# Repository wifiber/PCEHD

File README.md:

PC Engine / Turbo Grafx HDMI output board (PCEHD)
==============

Overview
--------------------------
PCEHD is a project to deliver HDMI video/audio from the PC Engine/Turbo-Grafx utilizing the digital video bus exposed on the expansion connector. The goal is to take the digital video directly from the console and upscale it to 1080p.

Features
--------------------------
* None yet

TODO
--------------------------
* Finish initial verion of schematic (DONE)
* Finish initial verion of HDL code (need help here)
* Get test PCBs made (PENDING)
* Get HDMI video output working (PENDING)
* Get analog audio encoded into HDMI stream (PENDING)

Long Term TODO
--------------------------
* Optical Drive Emulation (PENDING)
* Flash cart / SD card option (PENDING)

Installation
--------------------------
Attach PCEHD to the expansion port on your PC Engine or Turbo-Grafx console. Enjoy lag free 1080p.

Usage
--------------------------

More info and discussion
--------------------------
See the docs folder for a collection of PC Engine dev material.
There are good schematics online and the TurboGrafx-16 Unit Service Manual provides an excellent block diagram that really makes understanding the interaction of the 3 main HuC62xx chips much easier.

The aim of the PCEHD project is to reproduce the IC112 (HuC6260) inside the FPGA on the PCEHD. HuC6260, the Video Color Encoder, has an internal palette used for the background and sprites. It is made up of 512 9-bit entries. The first 256 entries are for the backgrounds and the last 256 are for the sprites. 
When the console first boots up, the VCE is initialized with palette data from the Hu Card by the CPU. According to the schematics, the data lines from the HU card all have pull-ups to 5v. This is why when you start the console with no game inserted you get a white screen - the VCE palette get filled with all 0xFF for the RGB data, which then returns white on the screen.

Requirement 1. - The FPGA needs to snoop on the CPU -> VCE communication when the console first boots. The FPGA needs to see what the CPU is loading into the VCE internal palette (All 512 entries). This is possible since both the data and address bus are exposed on the expansion connector. So the FPGA should have insight to the CPU -> VCE communication.
Using the FPGA core for the HuC6260, if we are connected to the same address and data bus as the physical VCE, we should be able to get the CPU to update both the physical VCE and the FPGA-VCE at the same time, since the FPGA-VCE is listening at the same address as the VCE inside the console.  

Once the console boots up and the CPU has successfully loaded the VCE pallette, the VDC now comes into play. The VDC and VCE share a 9-bit video bus (This is separate from the data bus the CPU used to load the palette in the steps above). 
The VDC will be placing data on the video bus, this data is a 9-bit address into the VCE palette (9-bits = 512 entries). The VCE takes these addresses, does the lookup into its palette and returns the 9-bit RGB code.  

Requirement 2. - The FPGA needs to snoop on the VDC -> VCE communication. The VDC will be placing addresses on the video bus. Those addresses reference colors stored in the 512 entry VCE palette table. Once the VCE looks up the address, the data it returns is 9-bit RGB data. This 9-bit RGB data is used inside the HuC6260 to generate the analog RGB and composite signals. Assuming the FPGA knows what RGB values are stored in each VCE table entry.(Req 1)
Also, assuming the FPGA knows what the VCE will display next based on what palette address the VDC was placing on the video bus - we should be able to recreate the scanline that the VCE would have displayed. From there its a matter of line-doubling and tweaking to fit the 1080p standard.
Again, using the FPGA core for the HuC6260 should give us a VCE that acts just like the phyiscal one inside the console. Once we have the VCE outputting the RGB data, its a matter of formatting it into the correct HDMI standard.

Thanks to marqs for the OSSC/CPS2_HDMI projects that are the majority of the base material for this project
https://github.com/marqs85

Thanks to the FPGAPCE project on github for a nice HDL example of the entire console.
https://github.com/Torlus/FPGAPCE

Thanks to skum for the very clean and well layed out KiCad symbol and footprint of the expansion connector. Its 69 pins but somehow his symbol is manageable.
https://github.com/skumlos/pcengine-rgb-addon

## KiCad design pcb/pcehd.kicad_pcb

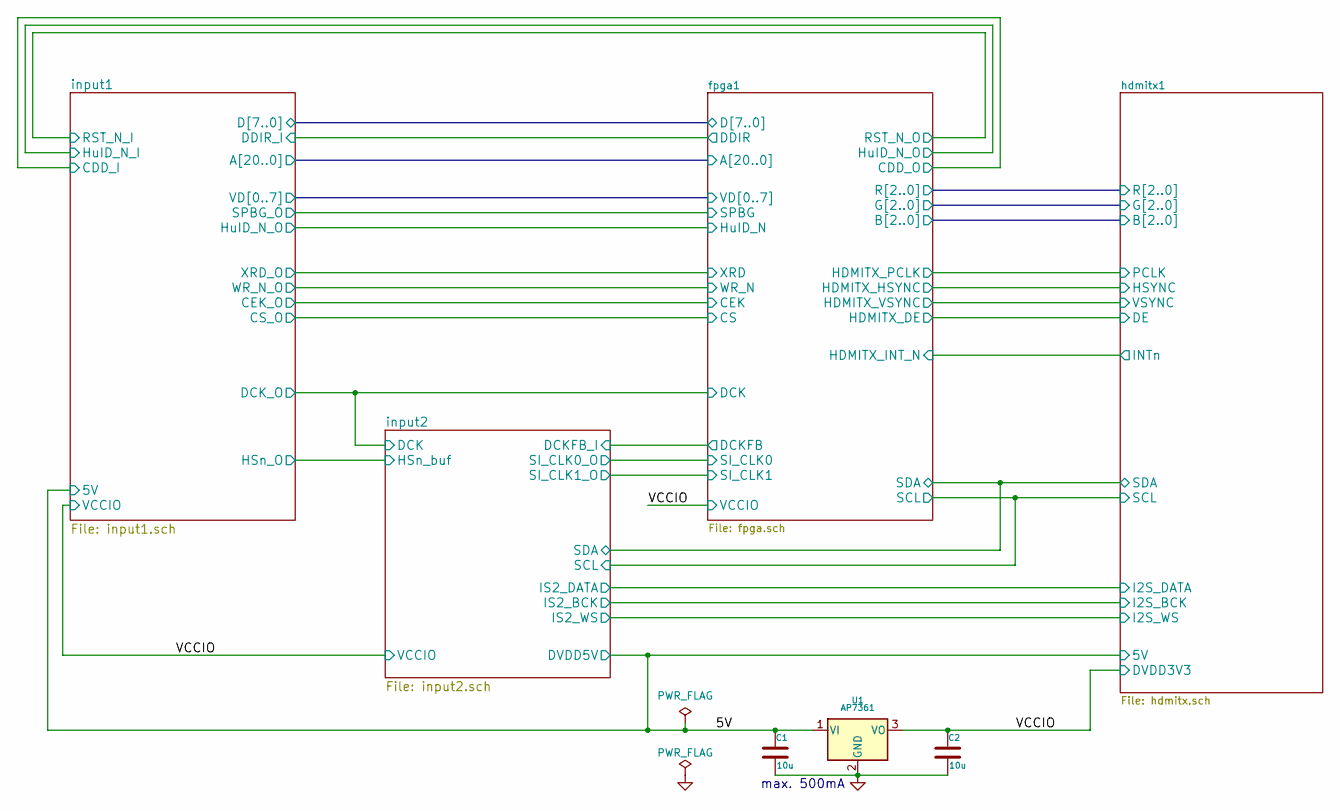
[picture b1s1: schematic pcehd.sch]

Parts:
C1, C2: 10u; SM0603_Capa_libcms
U1: AP7361; SOT-223_Handsoldering

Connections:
/5V: C1.1, U1.1 (VI); also elsewhere on the board
GND: C1.2, C2.2, U1.2 (GND); also elsewhere on the board
VCC: C2.1, U1.3 (VO); also elsewhere on the board

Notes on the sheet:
max. 500mA

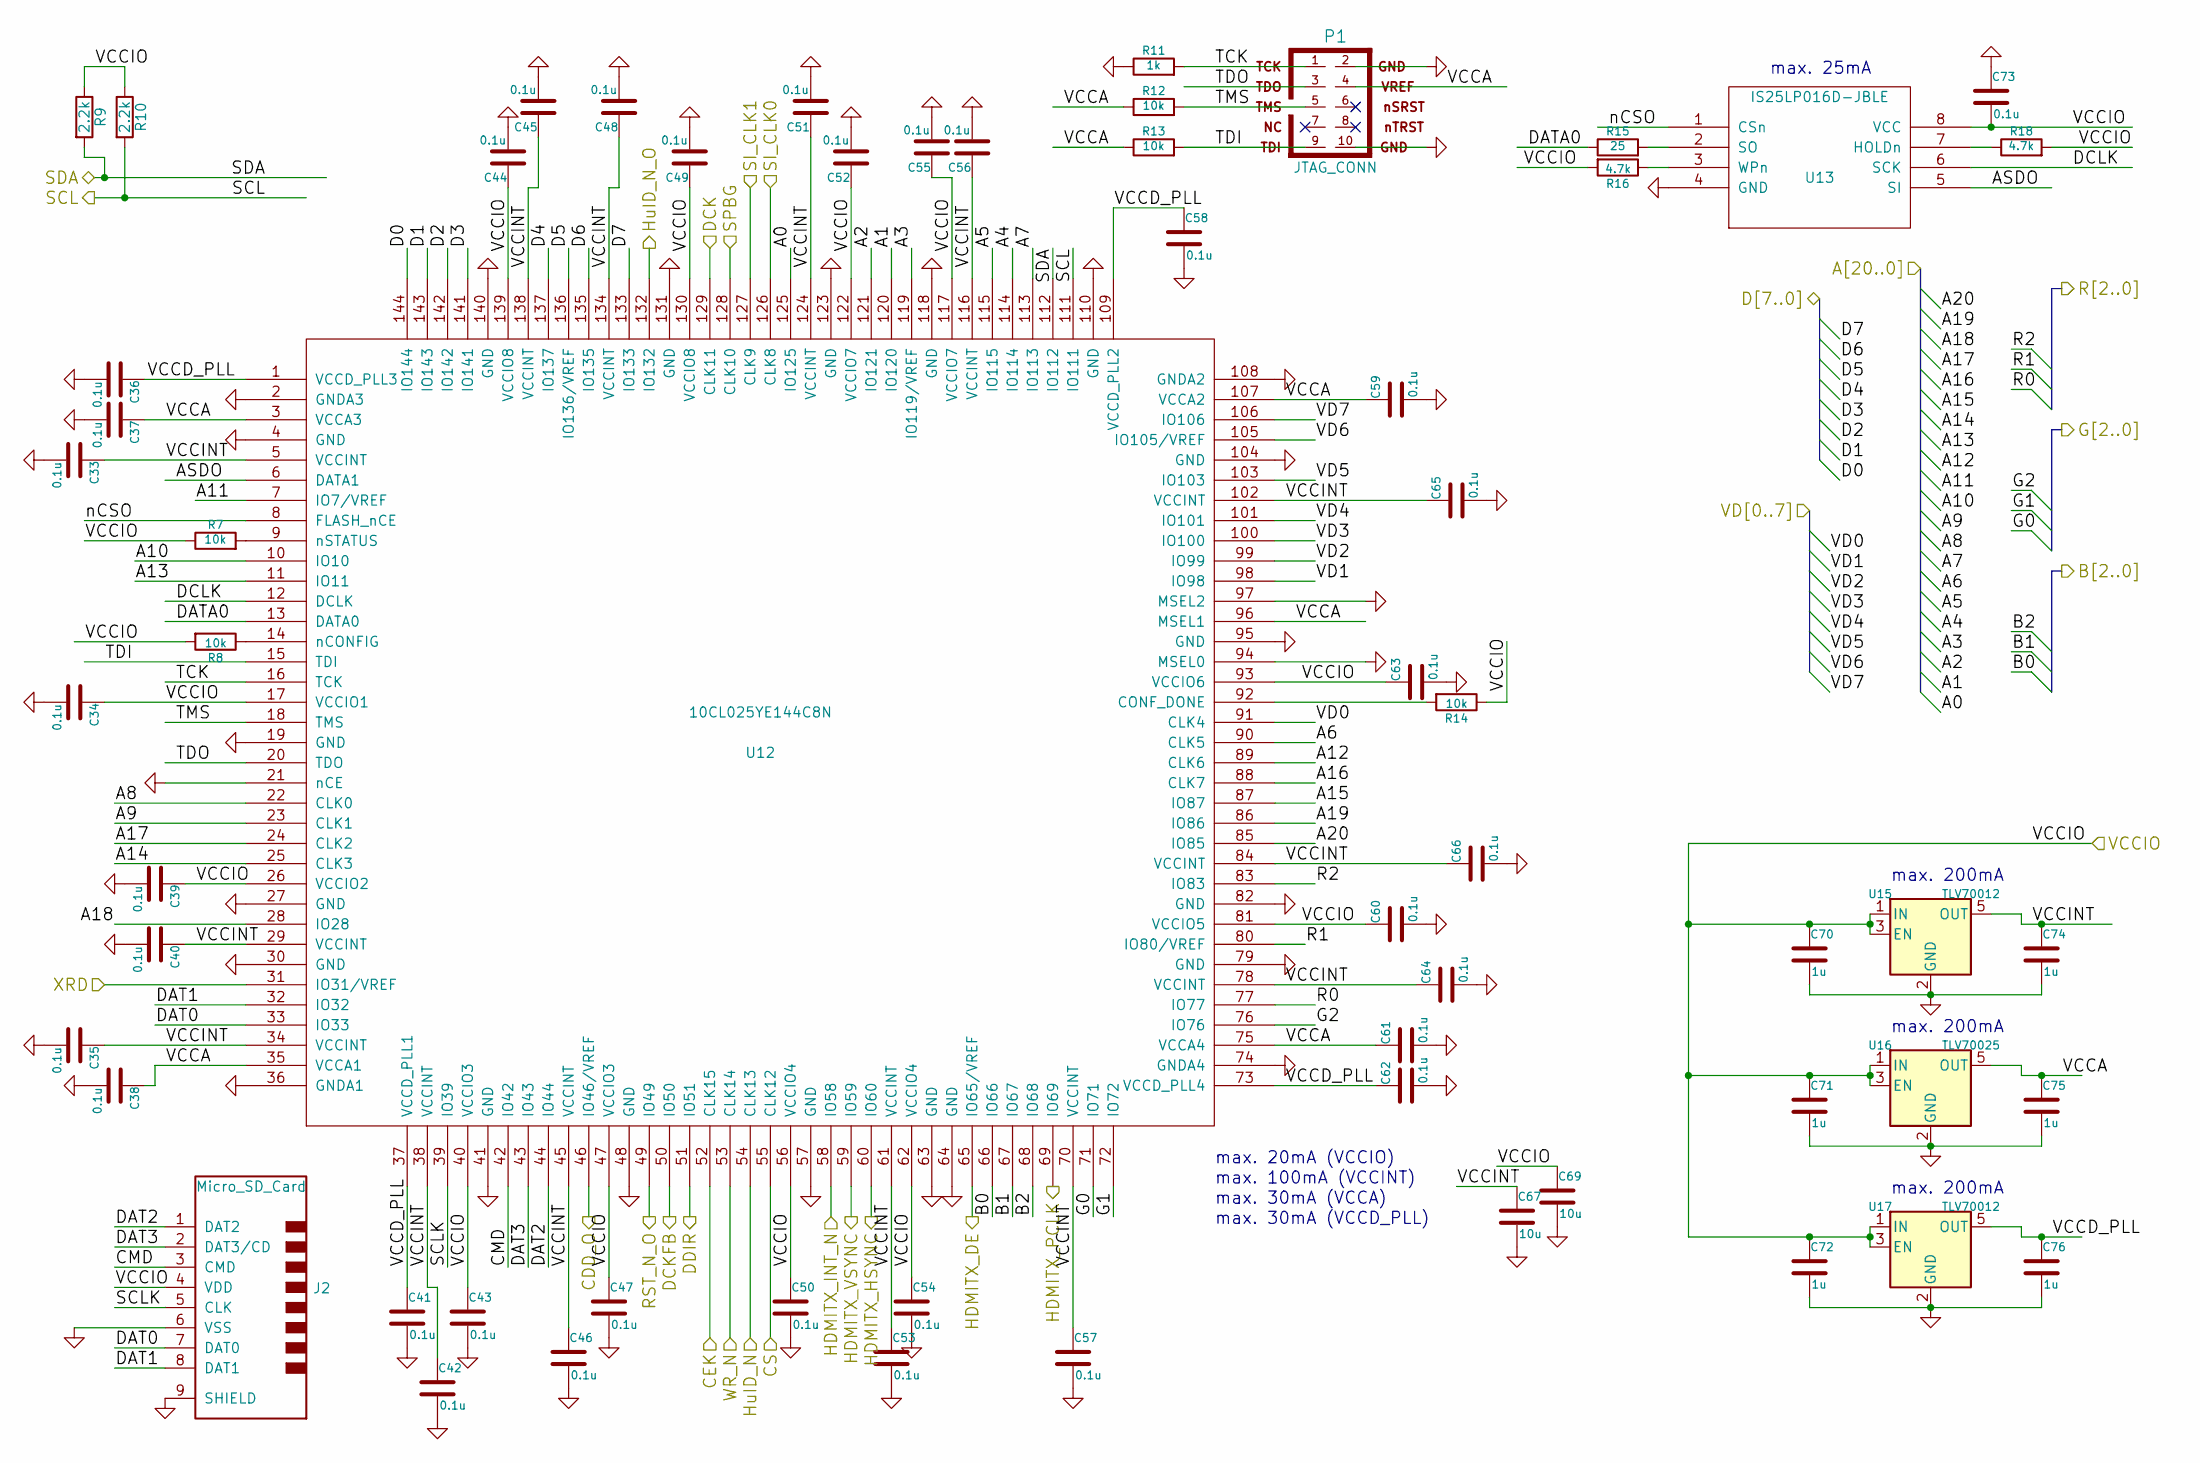
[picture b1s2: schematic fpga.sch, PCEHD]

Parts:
C33, C34, C35, C36, C37, C38, C39, C40, C41, C42, C43, C44, C45, C46, C47, C48, C49, C50, C51, C52, C53, C54, C55, C56, C57, C58, C59, C60, C61, C62, C63, C64, C65, C66, C73: 0.1u; SM0603_Capa_libcms
C67, C69: 10u; SM0603_Capa_libcms
C70, C71, C72, C74, C75, C76: 1u; SM0603_Capa_libcms
J2: Micro_SD_Card; microSD_HC_Hirose_DM3D-SF
P1: JTAG_CONN; IDC-Header_2x05_P2.54mm_Vertical
R7, R8, R12, R13, R14: 10k; SM0603_Resistor_libcms
R9, R10: 2.2k; SM0603_Resistor_libcms
R11: 1k; SM0603_Resistor_libcms
R15: 25; SM0603_Resistor_libcms
R16, R18: 4.7k; SM0603_Resistor_libcms
U12: 10CL025YE144C8N; TQFP-144_thermal
U13: IS25LP016D-JBLE; SOIC-8_3.9x4.9mm_Pitch1.27mm_Handsoldering
U15, U17: TLV70012; SOT-23-5_Handsoldering
U16: TLV70025; SOT-23-5_Handsoldering

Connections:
/fpga1/A0: U12.125 (IO125); also elsewhere on the board
/fpga1/A1: U12.120 (IO120); also elsewhere on the board
/fpga1/A2: U12.121 (IO121); also elsewhere on the board
/fpga1/A3: U12.119 (IO119/VREF); also elsewhere on the board
/fpga1/A4: U12.114 (IO114); also elsewhere on the board
/fpga1/A5: U12.115 (IO115); also elsewhere on the board
/fpga1/A6: U12.90 (CLK5); also elsewhere on the board
/fpga1/A7: U12.113 (IO113); also elsewhere on the board
/fpga1/A8: U12.22 (CLK0); also elsewhere on the board
/fpga1/A9: U12.23 (CLK1); also elsewhere on the board
/fpga1/A10: U12.10 (IO10); also elsewhere on the board
/fpga1/A11: U12.7 (IO7/VREF); also elsewhere on the board
/fpga1/A12: U12.89 (CLK6); also elsewhere on the board
/fpga1/A13: U12.11 (IO11); also elsewhere on the board
/fpga1/A14: U12.25 (CLK3); also elsewhere on the board
/fpga1/A15: U12.87 (IO87); also elsewhere on the board
/fpga1/A16: U12.88 (CLK7); also elsewhere on the board
/fpga1/A17: U12.24 (CLK2); also elsewhere on the board
/fpga1/A18: U12.28 (IO28); also elsewhere on the board
/fpga1/A19: U12.86 (IO86); also elsewhere on the board
/fpga1/A20: U12.85 (IO85); also elsewhere on the board
/fpga1/ASDO: U12.6 (DATA1), U13.5 (SI)
/fpga1/B0: U12.66 (IO66); also elsewhere on the board
/fpga1/B1: U12.67 (IO67); also elsewhere on the board
/fpga1/B2: U12.68 (IO68); also elsewhere on the board
/fpga1/CEK: U12.52 (CLK15); also elsewhere on the board
/fpga1/CMD: J2.3 (CMD), U12.42 (IO42)
/fpga1/CS: U12.55 (CLK12); also elsewhere on the board
/fpga1/D0: U12.144 (IO144); also elsewhere on the board
/fpga1/D1: U12.143 (IO143); also elsewhere on the board
/fpga1/D2: U12.142 (IO142); also elsewhere on the board
/fpga1/D3: U12.141 (IO141); also elsewhere on the board
/fpga1/D4: U12.137 (IO137); also elsewhere on the board
/fpga1/D5: U12.136 (IO136/VREF); also elsewhere on the board
/fpga1/D6: U12.135 (IO135); also elsewhere on the board
/fpga1/D7: U12.133 (IO133); also elsewhere on the board
/fpga1/DAT0: J2.7 (DAT0), U12.33 (IO33)
/fpga1/DAT1: J2.8 (DAT1), U12.32 (IO32)
/fpga1/DAT2: J2.1 (DAT2), U12.44 (IO44)
/fpga1/DAT3: J2.2 (DAT3/CD), U12.43 (IO43)
/fpga1/DATA0: R15.1, U12.13 (DATA0)
/fpga1/DCK: U12.129 (CLK11); also elsewhere on the board
/fpga1/DCKFB: U12.50 (IO50); also elsewhere on the board
/fpga1/DCLK: U12.12 (DCLK), U13.6 (SCK)
/fpga1/DDIR: U12.51 (IO51); also elsewhere on the board
/fpga1/G0: U12.71 (IO71); also elsewhere on the board
/fpga1/G1: U12.72 (IO72); also elsewhere on the board
/fpga1/G2: U12.76 (IO76); also elsewhere on the board
/fpga1/HDMITX_HSYNC: U12.60 (IO60); also elsewhere on the board
/fpga1/HDMITX_INT_N: U12.58 (IO58); also elsewhere on the board
/fpga1/HDMITX_PCLK: U12.69 (IO69); also elsewhere on the board
/fpga1/HDMITX_VSYNC: U12.59 (IO59); also elsewhere on the board
/fpga1/HuID_N: U12.54 (CLK13); also elsewhere on the board
/fpga1/R0: U12.77 (IO77); also elsewhere on the board
/fpga1/R1: U12.80 (IO80/VREF); also elsewhere on the board
/fpga1/R2: U12.83 (IO83); also elsewhere on the board
/fpga1/SCL: R10.2, U12.111 (IO111); also elsewhere on the board
/fpga1/SCLK: J2.5 (CLK), U12.39 (IO39)
/fpga1/SDA: R9.2, U12.112 (IO112); also elsewhere on the board
/fpga1/SI_CLK0: U12.126 (CLK8); also elsewhere on the board
/fpga1/SI_CLK1: U12.127 (CLK9); also elsewhere on the board
/fpga1/SPBG: U12.128 (CLK10); also elsewhere on the board
/fpga1/TCK: P1.1, R11.2, U12.16 (TCK)
/fpga1/TDI: P1.9, R13.2, U12.15 (TDI)
/fpga1/TDO: P1.3, U12.20 (TDO)
/fpga1/TMS: P1.5, R12.2, U12.18 (TMS)
/fpga1/VCCA: C37.1, C38.1, C59.1, C61.1, C75.1, P1.4, R12.1, R13.1, U12.3 (VCCA3), U12.35 (VCCA1), U12.75 (VCCA4), U12.96 (MSEL1), U12.107 (VCCA2), U16.5 (OUT)
/fpga1/VCCD_PLL: C36.1, C41.1, C58.1, C62.1, C76.1, U12.1 (VCCD_PLL3), U12.37 (VCCD_PLL1), U12.73 (VCCD_PLL4), U12.109 (VCCD_PLL2), U17.5 (OUT)
/fpga1/VCCINT: C33.1, C35.1, C40.1, C42.1, C45.1, C46.1, C48.1, C51.1, C53.1, C56.1, C57.1, C64.1, C65.1, C66.1, C67.1, C74.1, U12.5 (VCCINT), U12.29 (VCCINT), U12.34 (VCCINT), U12.38 (VCCINT), U12.45 (VCCINT), U12.61 (VCCINT), U12.70 (VCCINT), U12.78 (VCCINT), U12.84 (VCCINT), U12.102 (VCCINT), U12.116 (VCCINT), U12.124 (VCCINT), U12.134 (VCCINT), U12.138 (VCCINT), U15.5 (OUT)
/fpga1/VD0: U12.91 (CLK4); also elsewhere on the board
/fpga1/VD1: U12.98 (IO98); also elsewhere on the board
/fpga1/VD2: U12.99 (IO99); also elsewhere on the board
/fpga1/VD3: U12.100 (IO100); also elsewhere on the board
/fpga1/VD4: U12.101 (IO101); also elsewhere on the board
/fpga1/VD5: U12.103 (IO103); also elsewhere on the board
/fpga1/VD6: U12.105 (IO105/VREF); also elsewhere on the board
/fpga1/VD7: U12.106 (IO106); also elsewhere on the board
/fpga1/WR_N: U12.53 (CLK14); also elsewhere on the board
/fpga1/XRD: U12.31 (IO31/VREF); also elsewhere on the board
/fpga1/nCSO: U12.8 (FLASH_nCE), U13.1 (CSn)
/hdmitx1/DE: U12.65 (IO65/VREF); also elsewhere on the board
/input1/CDD_I: U12.46 (IO46/VREF); also elsewhere on the board
/input1/HuID_N_I: U12.132 (IO132); also elsewhere on the board
/input1/RST_N_I: U12.49 (IO49); also elsewhere on the board
GND: C33.2, C34.2, C35.2, C36.2, C37.2, C38.2, C39.2, C40.2, C41.2, C42.2, C43.2, C44.2, C45.2, C46.2, C47.2, C48.2, C49.2, C50.2, C51.2, C52.2, C53.2, C54.2, C55.2, C56.2, C57.2, C58.2, C59.2, C60.2, C61.2, C62.2, C63.2, C64.2, C65.2, C66.2, C67.2, C69.2, C70.2, C71.2, C72.2, C73.1, C74.2, C75.2, C76.2, J2.6 (VSS), J2.9 (SHIELD), P1.2, P1.10, R11.1, U12.2 (GNDA3), U12.4 (GND), U12.19 (GND), U12.21 (nCE), U12.27 (GND), U12.30 (GND), U12.36 (GNDA1), U12.41 (GND), U12.48 (GND), U12.57 (GND), U12.63 (GND), U12.64 (GND), U12.74 (GNDA4), U12.79 (GND), U12.82 (GND), U12.94 (MSEL0), U12.95 (GND), U12.97 (MSEL2), U12.104 (GND), U12.108 (GNDA2), U12.110 (GND), U12.118 (GND), U12.123 (GND), U12.131 (GND), U12.140 (GND), U13.4 (GND), U15.2 (GND), U16.2 (GND), U17.2 (GND); also elsewhere on the board
unnamed: R7.2, U12.9 (nSTATUS)
unnamed: R8.1, U12.14 (nCONFIG)
unnamed: R14.2, U12.92 (CONF_DONE)
unnamed: R15.2, U13.2 (SO)
unnamed: R16.1, U13.3 (WPn)
unnamed: R18.1, U13.7 (HOLDn)
VCC: C34.1, C39.1, C43.1, C44.1, C47.1, C49.1, C50.1, C52.1, C54.1, C55.1, C60.1, C63.1, C69.1, C70.1, C71.1, C72.1, C73.2, J2.4 (VDD), R7.1, R8.2, R9.1, R10.1, R14.1, R16.2, R18.2, U12.17 (VCCIO1), U12.26 (VCCIO2), U12.40 (VCCIO3), U12.47 (VCCIO3), U12.56 (VCCIO4), U12.62 (VCCIO4), U12.81 (VCCIO5), U12.93 (VCCIO6), U12.117 (VCCIO7), U12.122 (VCCIO7), U12.130 (VCCIO8), U12.139 (VCCIO8), U13.8 (VCC), U15.1 (IN), U15.3 (EN), U16.1 (IN), U16.3 (EN), U17.1 (IN), U17.3 (EN); also elsewhere on the board

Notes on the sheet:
max. 200mA
max. 25mA
max. 20mA (VCCIO)
max. 100mA (VCCINT)
max. 30mA (VCCA)
max. 30mA (VCCD_PLL)

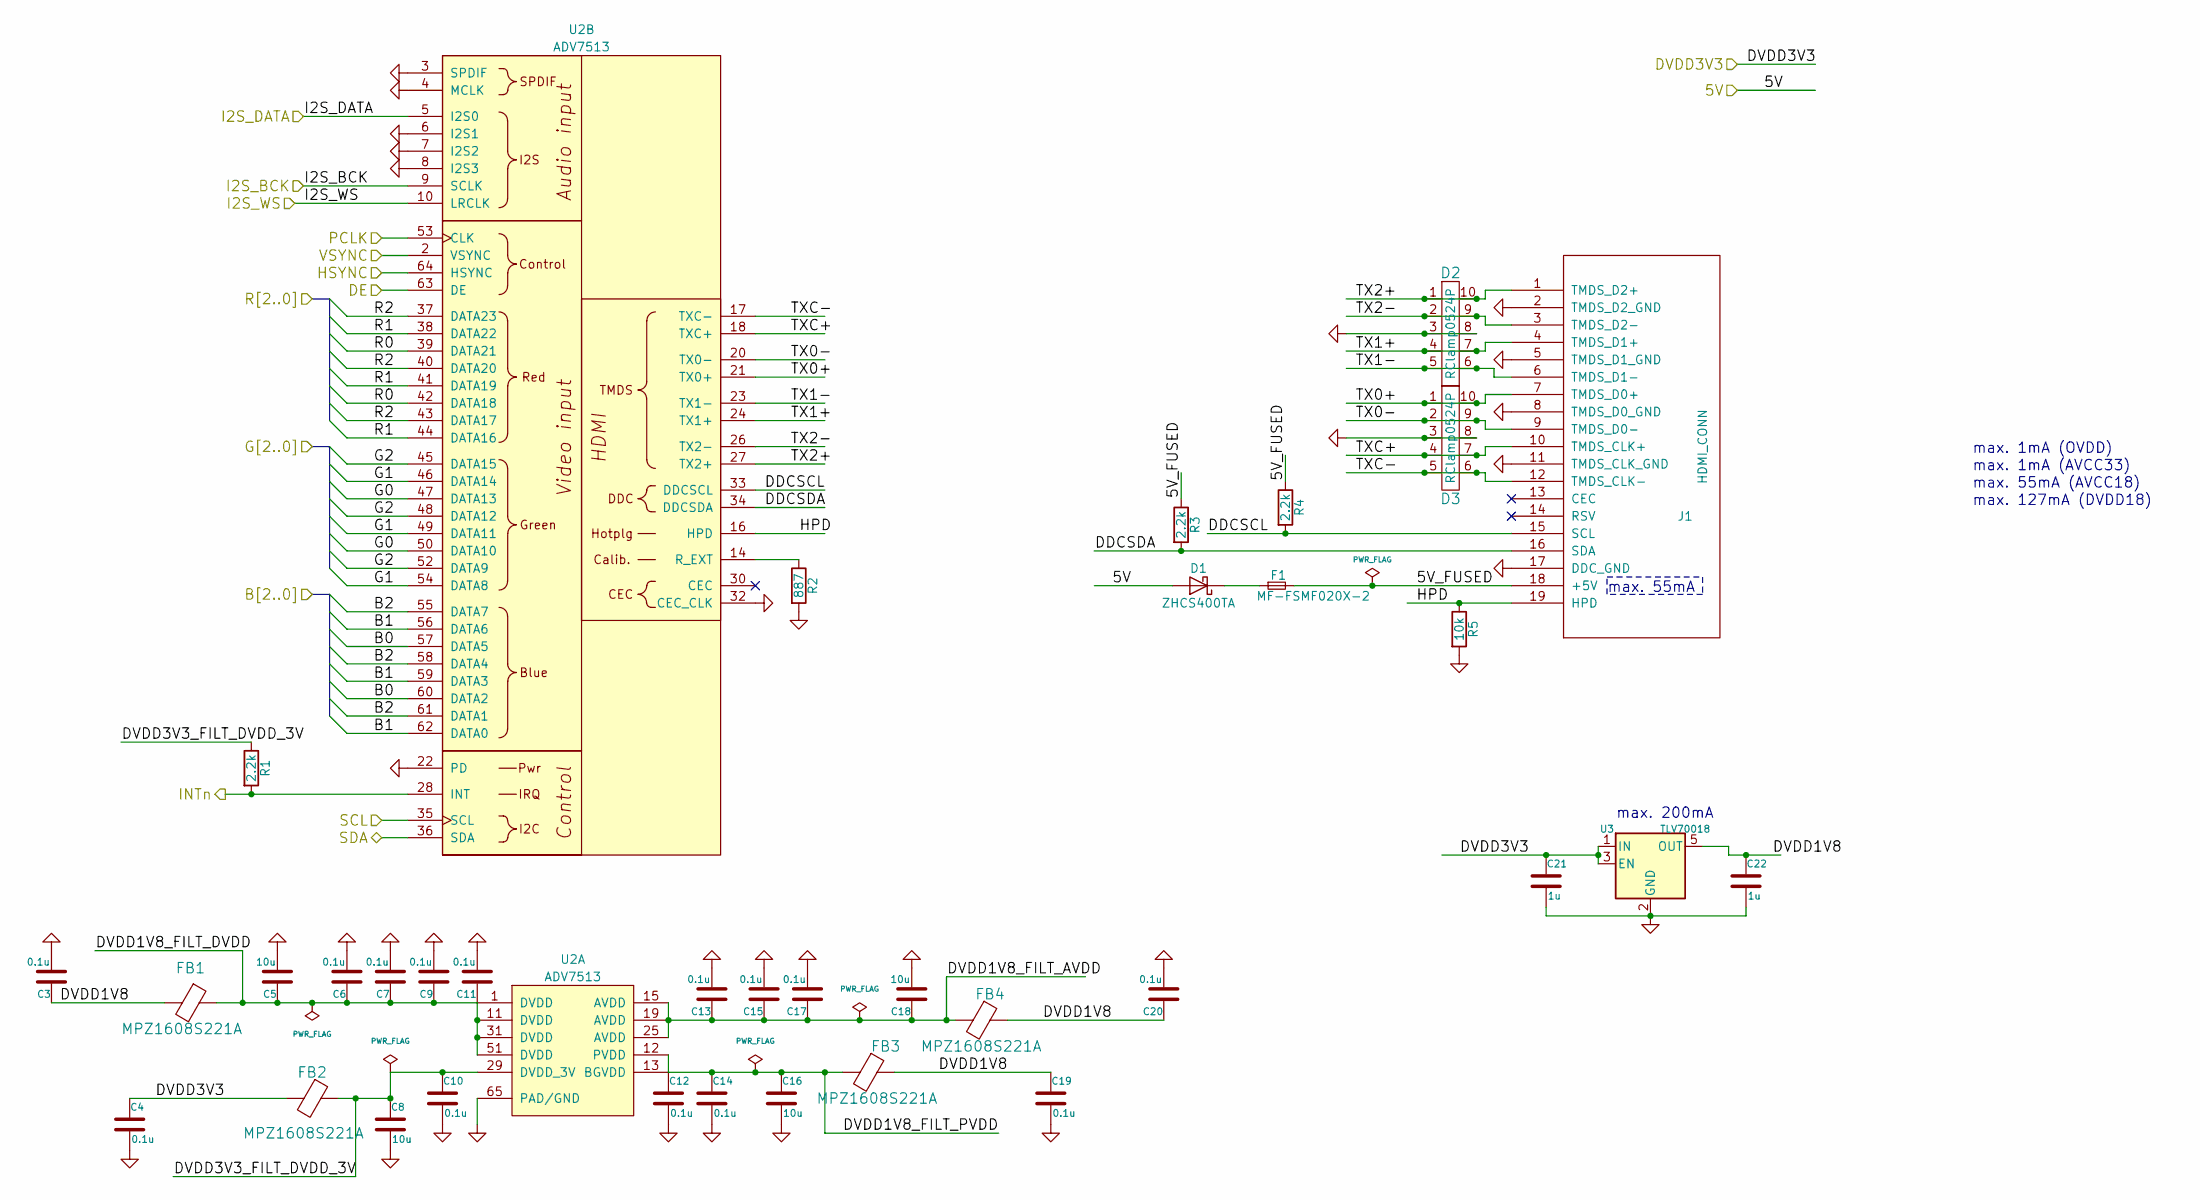
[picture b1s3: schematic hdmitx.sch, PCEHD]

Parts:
C3, C4, C6, C7, C9, C10, C11, C12, C13, C14, C15, C17, C19, C20: 0.1u; SM0603_Capa_libcms
C5, C8, C16, C18: 10u; SM0603_Capa_libcms
C21, C22: 1u; SM0603_Capa_libcms
D1: ZHCS400TA; SOD-323_Handsoldering
D2, D3: RClamp0524P; SLP2510P8
F1: MF-FSMF020X-2; SM0603_Resistor_libcms
FB1, FB2, FB3, FB4: MPZ1608S221A; SM0603_Resistor_libcms
J1: HDMI_CONN; HDMI_CONN-10029449-111RLF; Part ID 10029449-111RLF
R1, R3, R4: 2.2k; SM0603_Resistor_libcms
R2: 887; SM0603_Resistor_libcms
R5: 10k; SM0603_Resistor_libcms
U2: ADV7513; LQFP-64-1EP_10x10mm_Pitch0.5mm_Handsoldering
U3: TLV70018; SOT-23-5_Handsoldering

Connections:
/5V: D1.2 (A); also elsewhere on the board
/fpga1/B0: U2.57 (DATA5), U2.60 (DATA2); also elsewhere on the board
/fpga1/B1: U2.56 (DATA6), U2.59 (DATA3), U2.62 (DATA0); also elsewhere on the board
/fpga1/B2: U2.55 (DATA7), U2.58 (DATA4), U2.61 (DATA1); also elsewhere on the board
/fpga1/G0: U2.47 (DATA13), U2.50 (DATA10); also elsewhere on the board
/fpga1/G1: U2.46 (DATA14), U2.49 (DATA11), U2.54 (DATA8); also elsewhere on the board
/fpga1/G2: U2.45 (DATA15), U2.48 (DATA12), U2.52 (DATA9); also elsewhere on the board
/fpga1/HDMITX_HSYNC: U2.64 (HSYNC); also elsewhere on the board
/fpga1/HDMITX_INT_N: R1.2, U2.28 (INT); also elsewhere on the board
/fpga1/HDMITX_PCLK: U2.53 (CLK); also elsewhere on the board
/fpga1/HDMITX_VSYNC: U2.2 (VSYNC); also elsewhere on the board
/fpga1/R0: U2.39 (DATA21), U2.42 (DATA18); also elsewhere on the board
/fpga1/R1: U2.38 (DATA22), U2.41 (DATA19), U2.44 (DATA16); also elsewhere on the board
/fpga1/R2: U2.37 (DATA23), U2.40 (DATA20), U2.43 (DATA17); also elsewhere on the board
/fpga1/SCL: U2.35 (SCL); also elsewhere on the board
/fpga1/SDA: U2.36 (SDA); also elsewhere on the board
/hdmitx1/5V_FUSED: F1.2, J1.18 (+5V), R3.1, R4.1
/hdmitx1/DDCSCL: J1.15 (SCL), R4.2, U2.33 (DDCSCL)
/hdmitx1/DDCSDA: J1.16 (SDA), R3.2, U2.34 (DDCSDA)
/hdmitx1/DE: U2.63 (DE); also elsewhere on the board
/hdmitx1/DVDD1V8: C3.1, C19.1, C20.1, C22.1, FB1.2, FB3.1, FB4.1, U3.5 (OUT)
/hdmitx1/DVDD1V8_FILT_AVDD: C13.1, C15.1, C17.1, C18.1, FB4.2, U2.15 (AVDD), U2.19 (AVDD), U2.25 (AVDD)
/hdmitx1/DVDD1V8_FILT_DVDD: C5.1, C6.1, C7.1, C9.1, C11.1, FB1.1, U2.1 (DVDD), U2.11 (DVDD), U2.31 (DVDD), U2.51 (DVDD)
/hdmitx1/DVDD1V8_FILT_PVDD: C12.1, C14.1, C16.1, FB3.2, U2.12 (PVDD), U2.13 (BGVDD)
/hdmitx1/DVDD3V3_FILT_DVDD_3V: C8.1, C10.1, FB2.1, R1.1, U2.29 (DVDD_3V)
/hdmitx1/HPD: J1.19 (HPD), R5.1, U2.16 (HPD)
/hdmitx1/I2S_BCK: U2.9 (SCLK); also elsewhere on the board
/hdmitx1/I2S_DATA: U2.5 (I2S0); also elsewhere on the board
/hdmitx1/I2S_WS: U2.10 (LRCLK); also elsewhere on the board
/hdmitx1/TX0+: D3.1, D3.10, J1.7 (TMDS_D0+), U2.21 (TX0+)
/hdmitx1/TX0-: D3.2, D3.9, J1.9 (TMDS_D0-), U2.20 (TX0-)
/hdmitx1/TX1+: D2.4, D2.7, J1.4 (TMDS_D1+), U2.24 (TX1+)
/hdmitx1/TX1-: D2.5, D2.6, J1.6 (TMDS_D1-), U2.23 (TX1-)
/hdmitx1/TX2+: D2.1, D2.10, J1.1 (TMDS_D2+), U2.27 (TX2+)
/hdmitx1/TX2-: D2.2, D2.9, J1.3 (TMDS_D2-), U2.26 (TX2-)
/hdmitx1/TXC+: D3.4, D3.7, J1.10 (TMDS_CLK+), U2.18 (TXC+)
/hdmitx1/TXC-: D3.5, D3.6, J1.12 (TMDS_CLK-), U2.17 (TXC-)
GND: C3.2, C4.2, C5.2, C6.2, C7.2, C8.2, C9.2, C10.2, C11.2, C12.2, C13.2, C14.2, C15.2, C16.2, C17.2, C18.2, C19.2, C20.2, C21.2, C22.2, D2.3, D2.8, D3.3, D3.8, J1.2 (TMDS_D2_GND), J1.5 (TMDS_D1_GND), J1.8 (TMDS_D0_GND), J1.11 (TMDS_CLK_GND), J1.17 (DDC_GND), R2.2, R5.2, U2.3 (SPDIF), U2.4 (MCLK), U2.6 (I2S1), U2.7 (I2S2), U2.8 (I2S3), U2.22 (PD), U2.32 (CEC_CLK), U2.65 (PAD/GND), U3.2 (GND); also elsewhere on the board
unnamed: D1.1 (K), F1.1
unnamed: R2.1, U2.14 (R_EXT)
VCC: C4.1, C21.1, FB2.2, U3.1 (IN), U3.3 (EN); also elsewhere on the board

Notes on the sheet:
max. 200mA
max. 1mA (OVDD)
max. 1mA (AVCC33)
max. 55mA (AVCC18)
max. 127mA (DVDD18)
max. 55mA

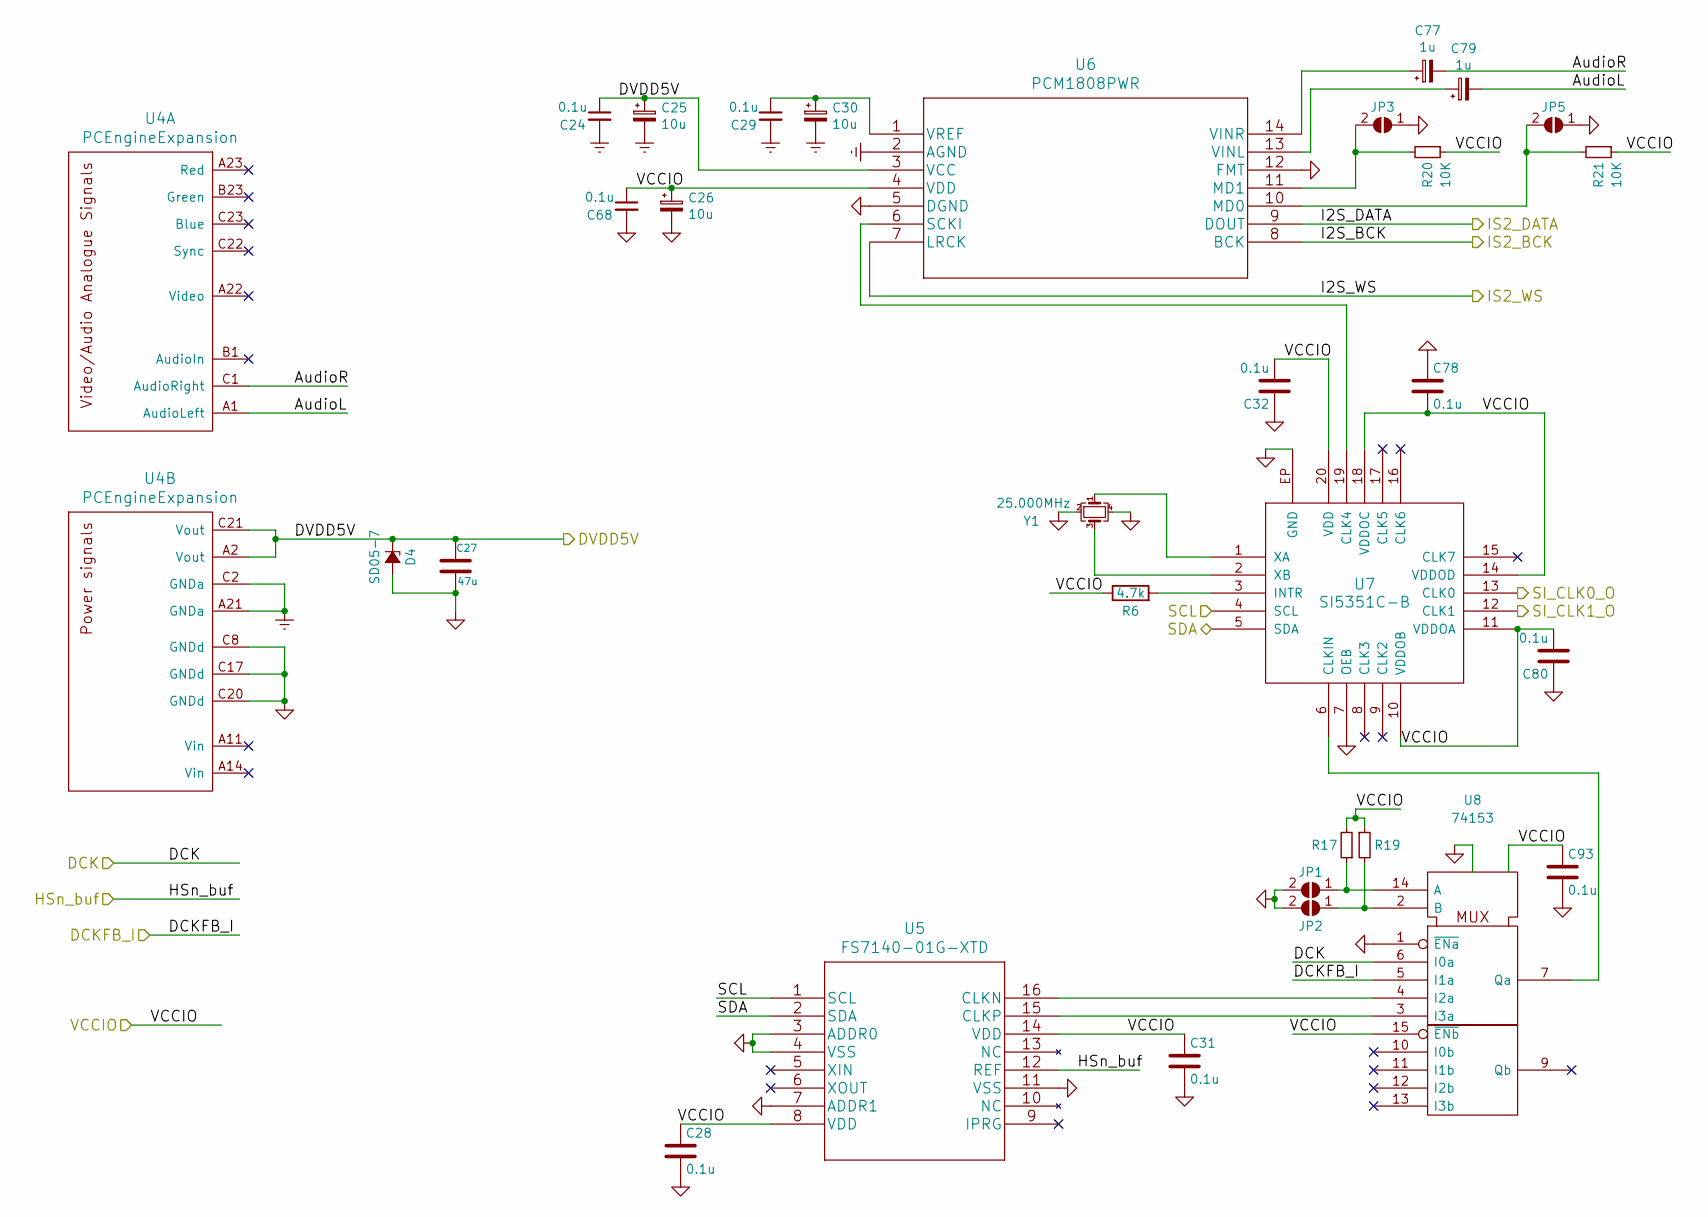
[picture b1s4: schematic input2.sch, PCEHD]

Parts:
C24, C28, C29, C31, C32, C68, C78, C80, C93: 0.1u; SM0603_Capa_libcms
C25, C26, C30: 10u; SM0603_Capa_libcms
C27: 47u; SM0603_Capa_libcms
C77, C79: 1u; SM0603_Capa_libcms
D4: SD05-7; SOD-323_Handsoldering
JP1, JP2, JP3, JP5: SolderJumper_2_Open; SolderJumper-2_P1.3mm_Open_RoundedPad1.0x1.5mm
R6: 4.7k; SM0603_Resistor_libcms
R17, R19, R20, R21: 10K; SM0603_Resistor_libcms
U4: PCEngineExpansion
U5: FS7140-01G-XTD
U6: PCM1808PWR
U7: SI5351C-B; QFN-20-1EP_4x4mm_Pitch0.5mm_Handsoldering
U8: 74153; SOIC-16_3.9x9.9mm_P1.27mm
Y1: 25.000MHz; Crystal_SMD_SeikoEpson_FA238-4Pin_3.2x2.5mm_HandSoldering

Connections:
/5V: C24.1, C25.1, C27.1, D4.1 (K), U4.A2 (Vout), U4.C21 (Vout), U6.3 (VCC); also elsewhere on the board
/fpga1/DCK: U8.6 (I0a); also elsewhere on the board
/fpga1/DCKFB: U8.5 (I1a); also elsewhere on the board
/fpga1/SCL: U5.1 (SCL), U7.4 (SCL); also elsewhere on the board
/fpga1/SDA: U5.2 (SDA), U7.5 (SDA); also elsewhere on the board
/fpga1/SI_CLK0: U7.13 (CLK0); also elsewhere on the board
/fpga1/SI_CLK1: U7.12 (CLK1); also elsewhere on the board
/hdmitx1/I2S_BCK: U6.8 (BCK); also elsewhere on the board
/hdmitx1/I2S_DATA: U6.9 (DOUT); also elsewhere on the board
/hdmitx1/I2S_WS: U6.7 (LRCK); also elsewhere on the board
/input1/HSn_O: U5.12 (REF); also elsewhere on the board
/input2/AudioL: C79.2, U4.A1 (AudioLeft)
/input2/AudioR: C77.2, U4.C1 (AudioRight)
GND: C26.2, C27.2, C28.2, C31.2, C32.1, C68.2, C78.1, C80.1, C93.2, D4.2 (A), JP1.2 (B), JP2.2 (B), JP3.1 (A), JP5.1 (A), U4.C8 (GNDd), U4.C17 (GNDd), U4.C20 (GNDd), U5.3 (ADDR0), U5.4 (VSS), U5.7 (ADDR1), U5.11 (VSS), U6.5 (DGND), U6.12 (FMT), U7.7 (OEB), U7.EP (GND), U8.1 (~ENa), U8.8 (GND), Y1.2, Y1.4; also elsewhere on the board
GNDREF: C24.2, C25.2, C29.2, C30.2, U4.A21 (GNDa), U4.C2 (GNDa), U6.2 (AGND)
unnamed: C29.1, C30.1, U6.1 (VREF)
unnamed: C77.1, U6.14 (VINR)
unnamed: C79.1, U6.13 (VINL)
unnamed: JP1.1 (A), R17.1, U8.14 (A)
unnamed: JP2.1 (A), R19.2, U8.2 (B)
unnamed: JP3.2 (B), R20.2, U6.11 (MD1)
unnamed: JP5.2 (B), R21.2, U6.10 (MD0)
unnamed: R6.2, U7.3 (INTR)
unnamed: U5.15 (CLKP), U8.3 (I3a)
unnamed: U5.16 (CLKN), U8.4 (I2a)
unnamed: U6.6 (SCKI), U7.19 (CLK4)
unnamed: U7.1 (XA), Y1.1
unnamed: U7.2 (XB), Y1.3
unnamed: U7.6 (CLKIN), U8.7 (Qa)
VCC: C26.1, C28.1, C31.1, C32.2, C68.1, C78.2, C80.2, C93.1, R6.1, R17.2, R19.1, R20.1, R21.1, U5.8 (VDD), U5.14 (VDD), U6.4 (VDD), U7.10 (VDDOB), U7.11 (VDDOA), U7.14 (VDDOD), U7.18 (VDDOC), U7.20 (VDD), U8.15 (~ENb), U8.16 (VCC); also elsewhere on the board

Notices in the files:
parts and their libraries:
Copyright 2016 Accelerated Designs. All rights reserved.
